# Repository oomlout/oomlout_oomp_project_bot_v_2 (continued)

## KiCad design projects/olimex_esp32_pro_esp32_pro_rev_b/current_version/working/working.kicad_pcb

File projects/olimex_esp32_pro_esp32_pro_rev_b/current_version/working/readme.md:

# esp32_pro
 
## summary 
* id: olimex_esp32_pro_esp32_pro_rev_b
* user: olimex
* name: esp32_pro
* board: esp32_pro_rev_b
* repo: https://github.com/OLIMEX/ESP32-PRO
* src_file_repo_kicad_pcb: HARDWARE/REV-B/ESP32-PRO_Rev_B.kicad_pcb
* src_file_repo_kicad_pcb_link: https://github.com/OLIMEX/ESP32-PRO/tree/master/HARDWARE/REV-B/ESP32-PRO_Rev_B.kicad_pcb

* src_file_repo_sch: HARDWARE/REV-B/ESP32-PRO_Rev_B.sch
* src_file_repo_sch_link: https://github.com/OLIMEX/ESP32-PRO/tree/master/HARDWARE/REV-B/ESP32-PRO_Rev_B.sch
* full details link: https://github.com/oomlout/oomlout_oomp_project_bot_v_2/tree/main/projects/olimex_esp32_pro_esp32_pro_rev_b/current_version/working

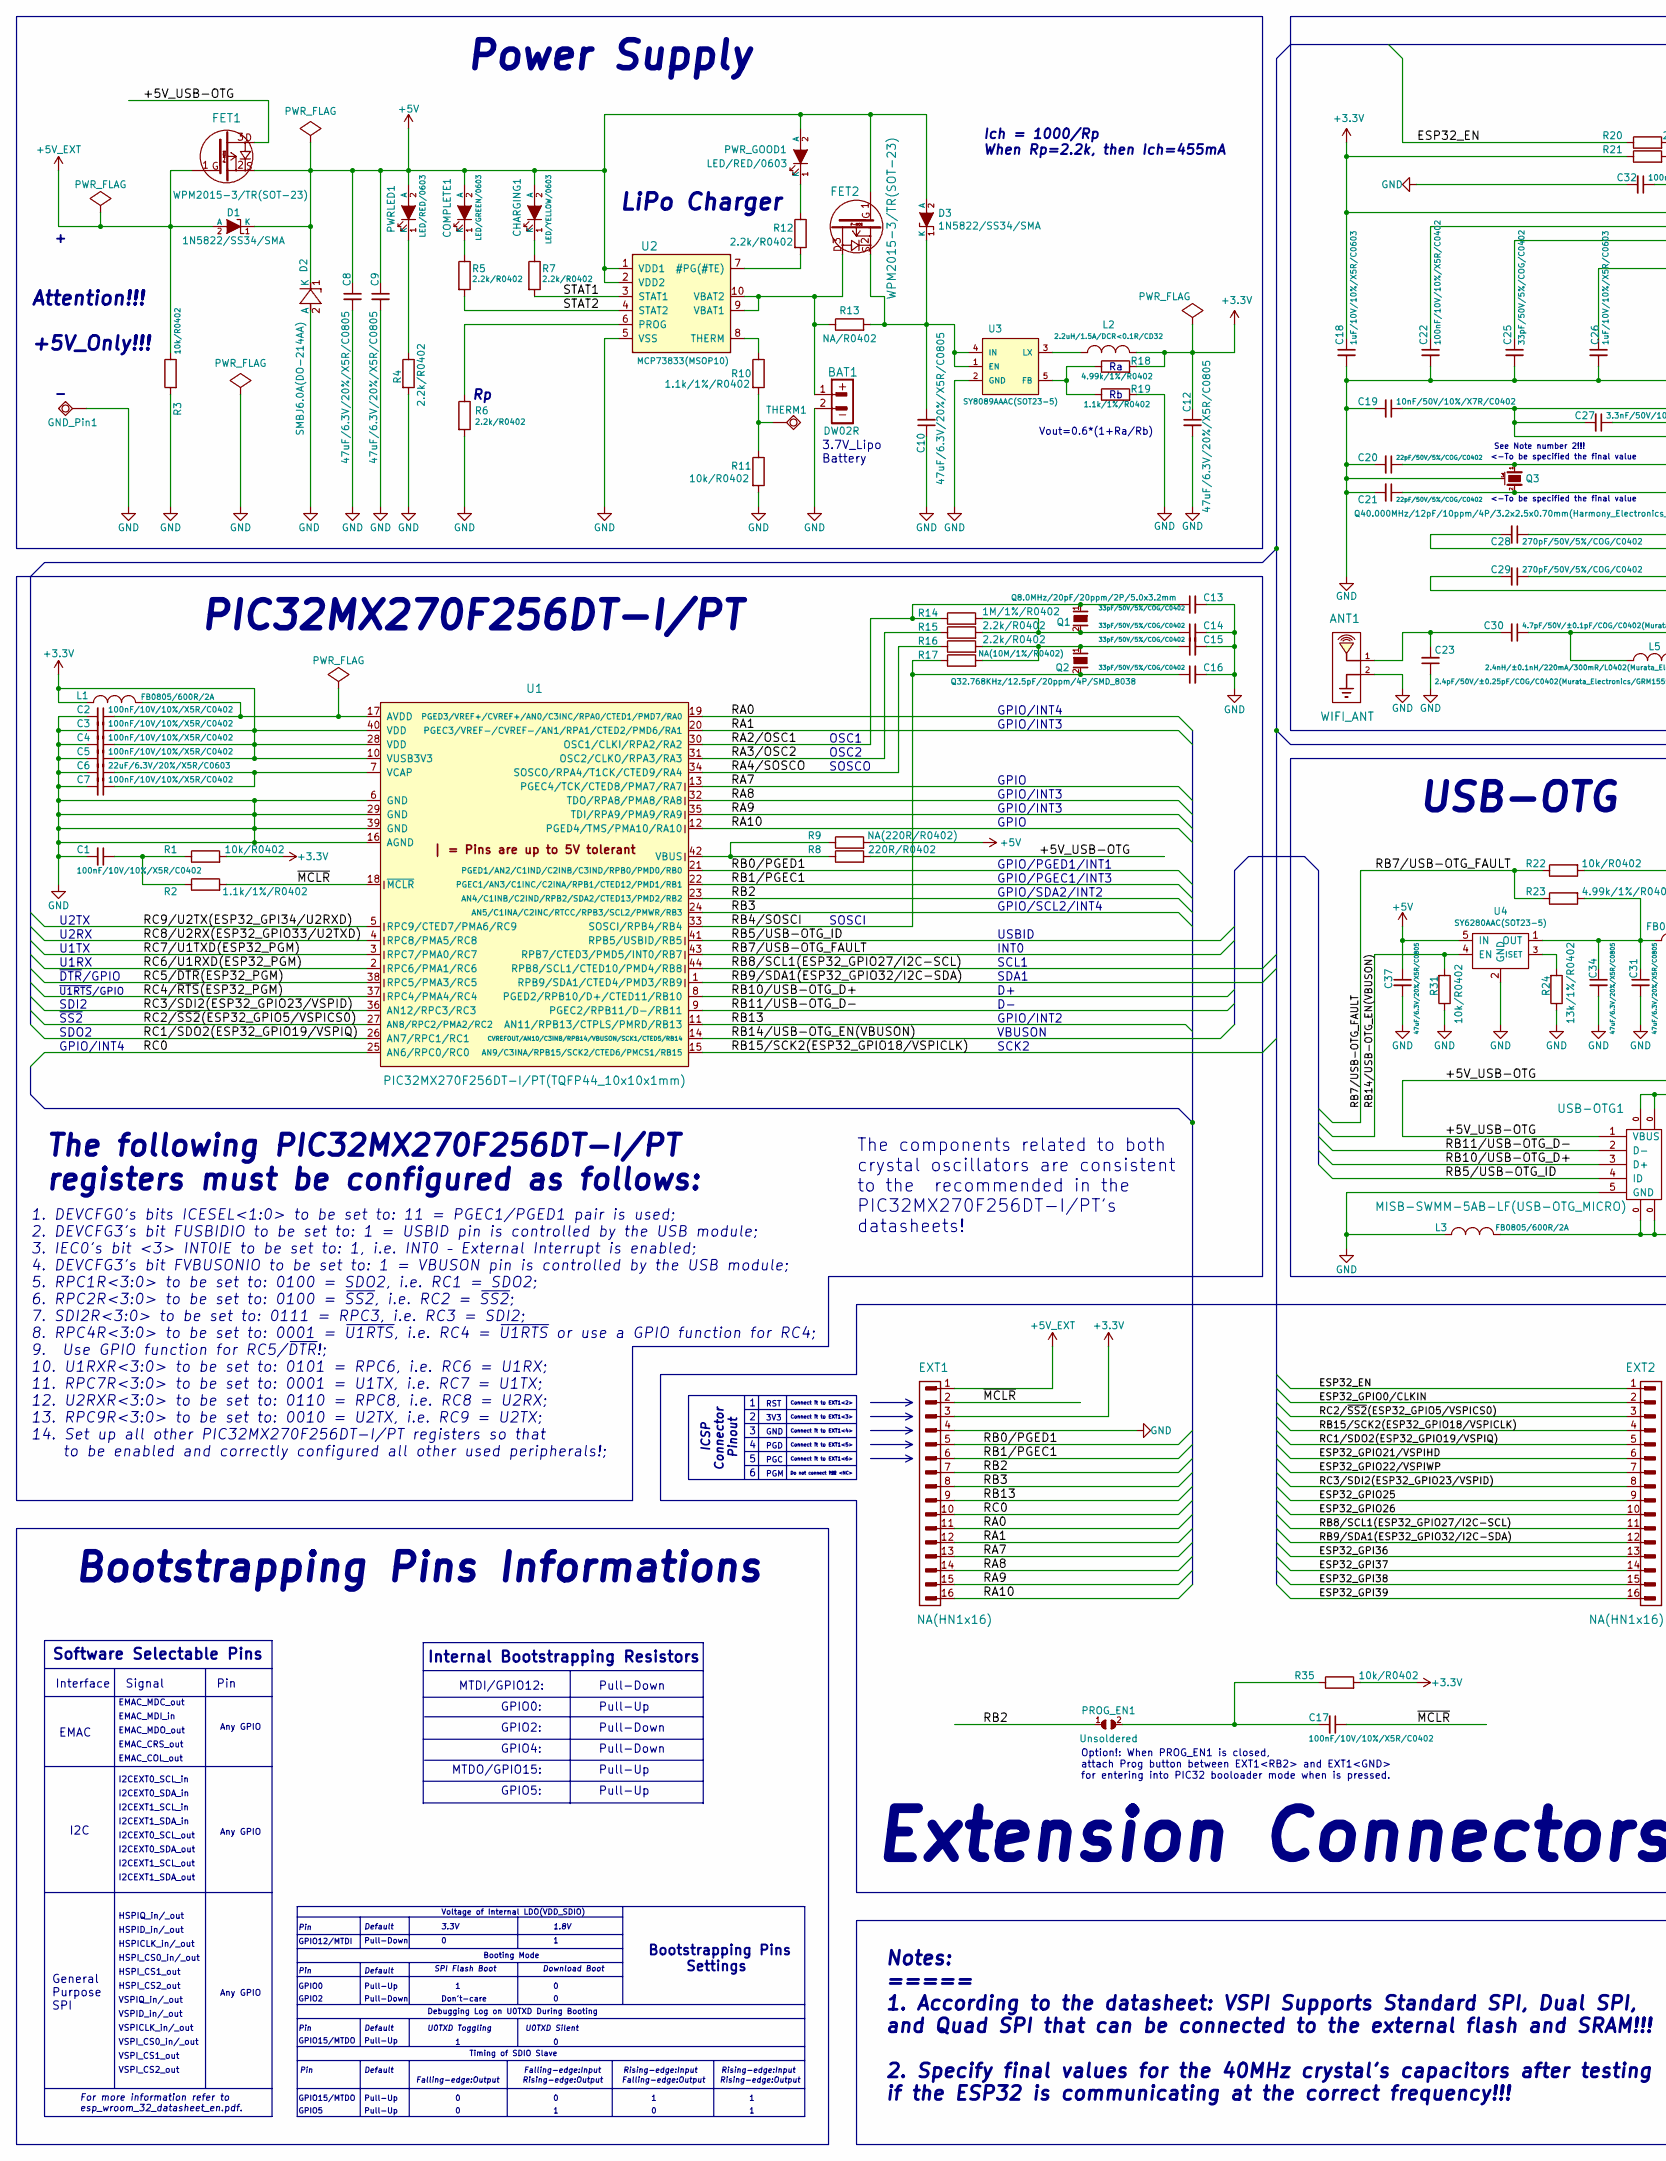
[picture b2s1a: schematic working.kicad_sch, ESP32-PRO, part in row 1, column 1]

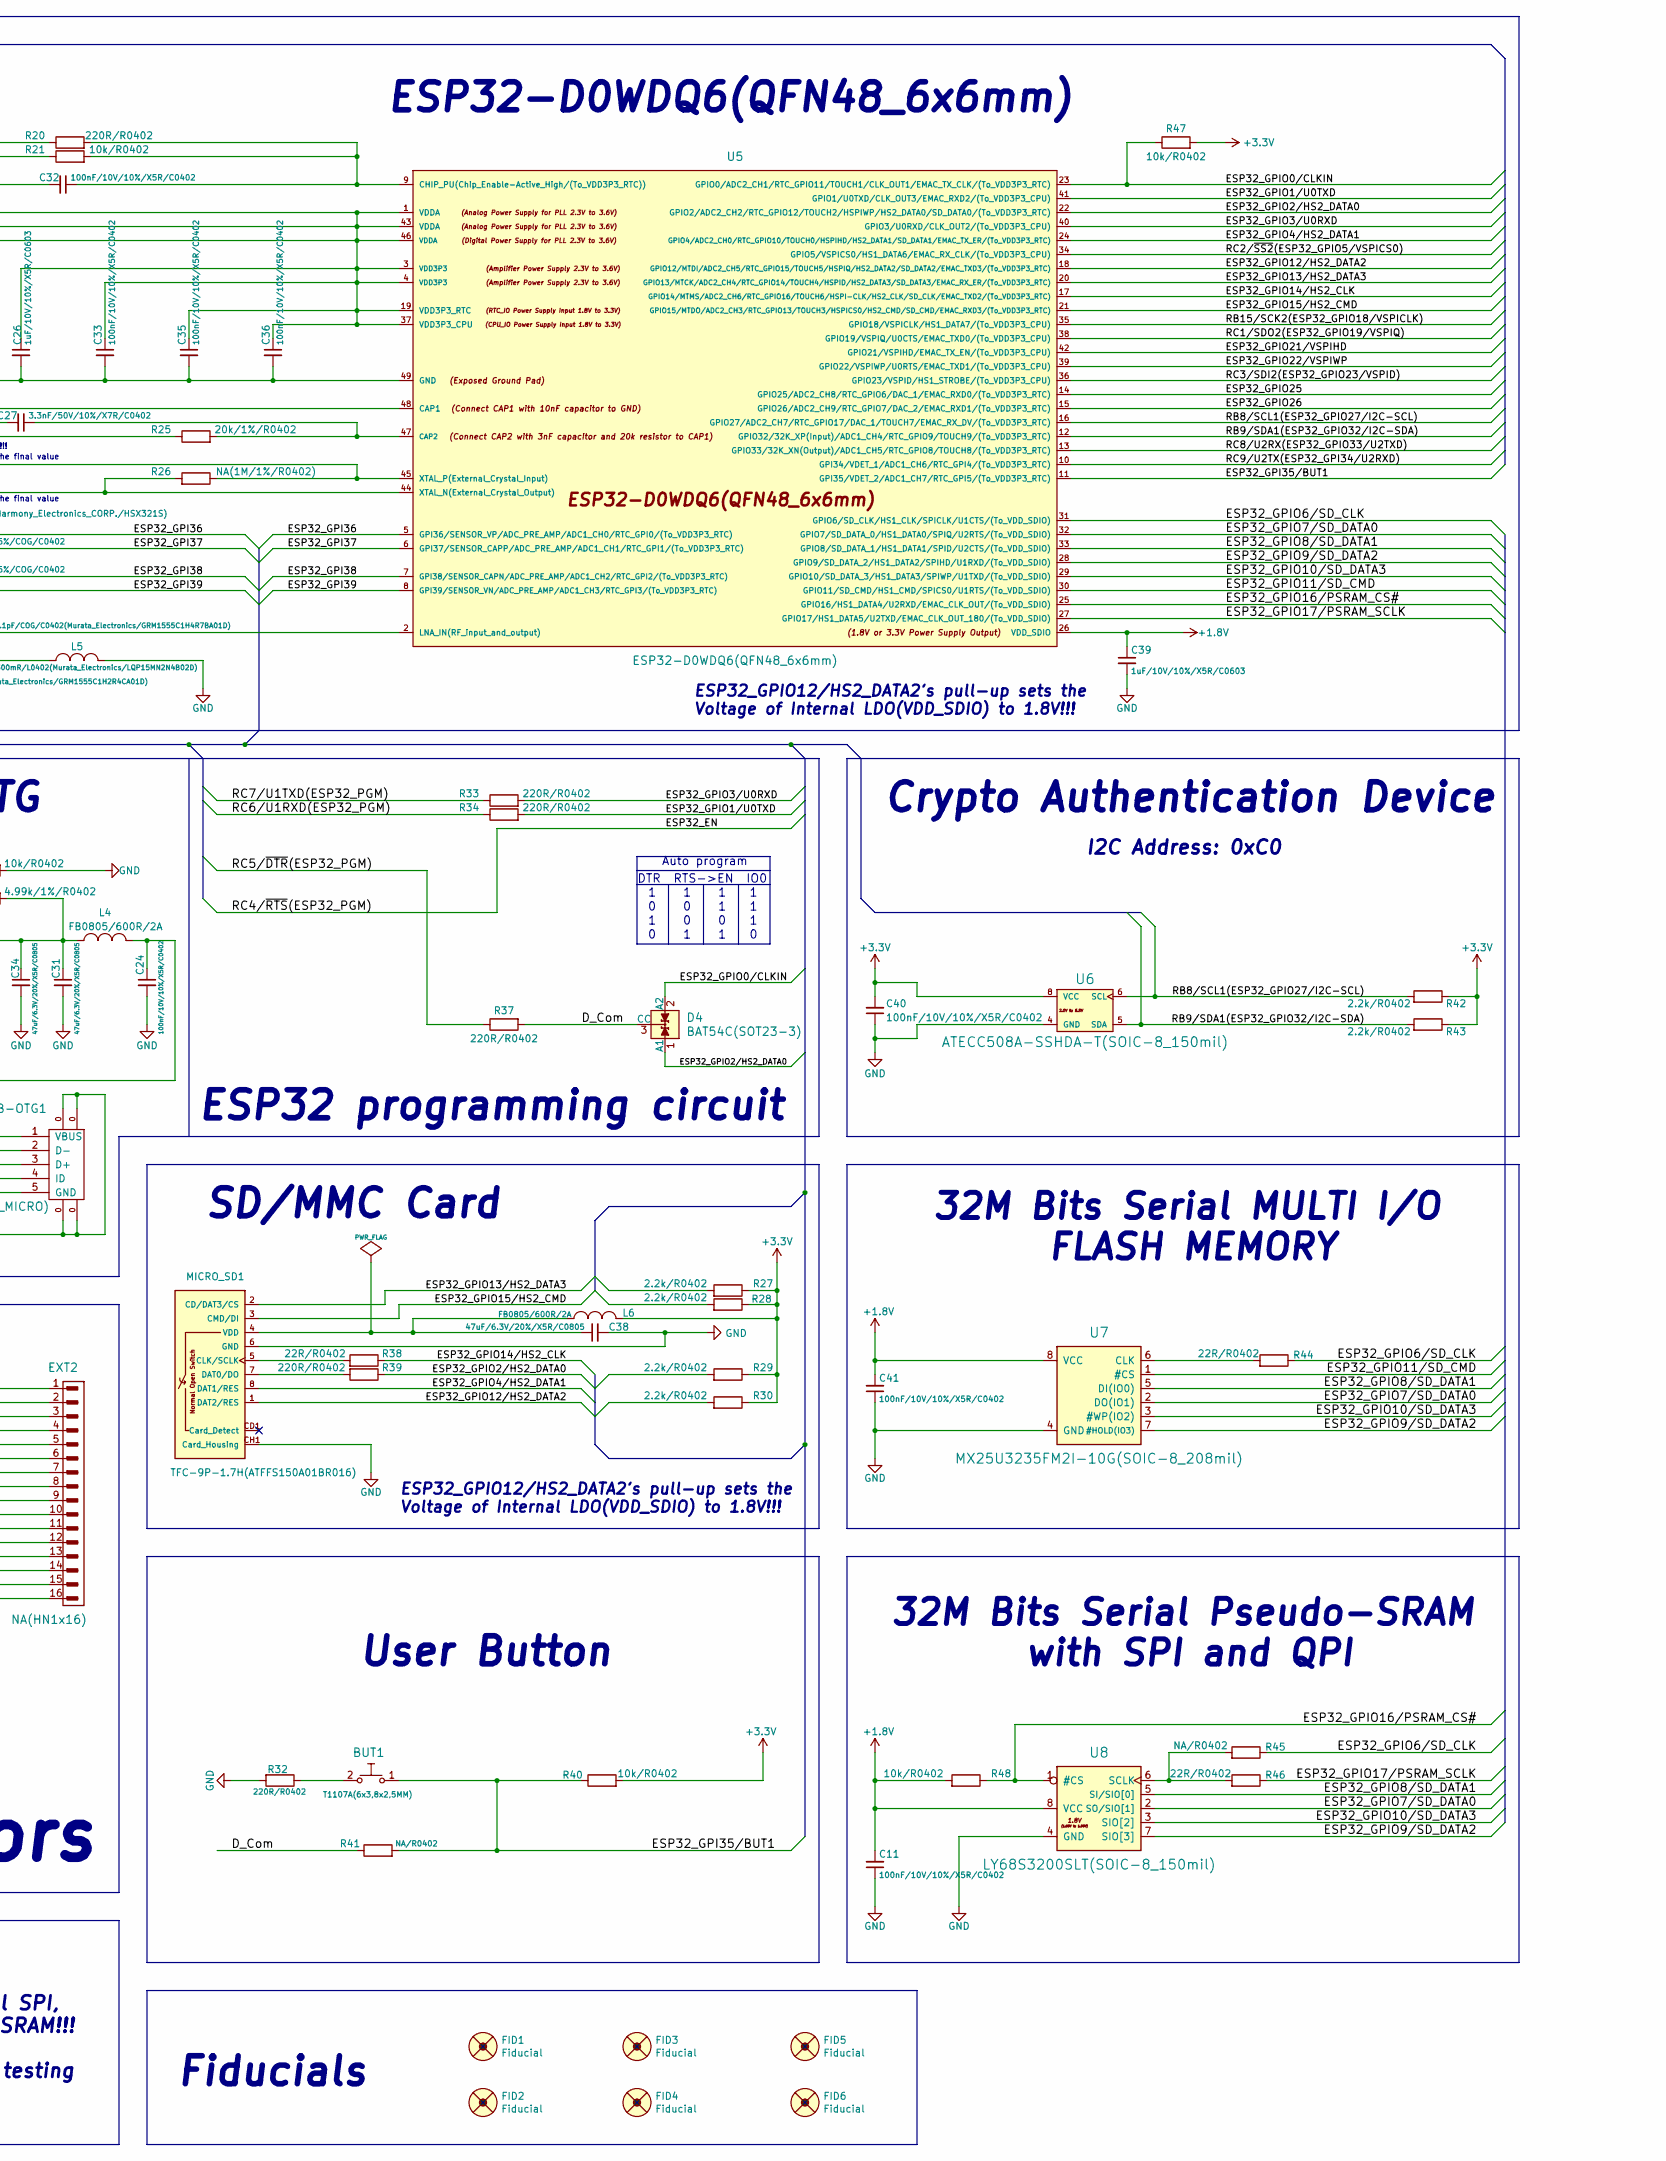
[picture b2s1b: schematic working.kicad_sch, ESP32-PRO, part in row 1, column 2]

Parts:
ANT1: WIFI_ANT; BT_Antenna_Inverted_1ANT_2GND
BAT1: DW02R; LIPO_BAT-CON2DW02R
BUT1: T1107A(6x3,8x2,5MM)
C1, C2, C3, C4, C5, C7, C11, C17, C22, C24, C32, C33, C35, C36, C40, C41: 100nF/10V/10%/X5R/C0402; C_0402_5MIL_DWS
C6: 22uF/6.3V/20%/X5R/C0603; C_0603_5MIL_DWS
C8, C9, C10, C12, C31, C34, C37, C38: 47uF/6.3V/20%/X5R/C0805; C_0805_5MIL_DWS
C13, C14, C15, C16, C25: 33pF/50V/5%/COG/C0402; C_0402_5MIL_DWS
C18, C26, C39: 1uF/10V/10%/X5R/C0603; C_0603_5MIL_DWS
C19: 10nF/50V/10%/X7R/C0402; C_0402_5MIL_DWS
C20, C21: 22pF/50V/5%/COG/C0402; C_0402_5MIL_DWS
C23: 2.4pF/50V/±0.25pF/COG/C0402(Murata_Electronics/GR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; C_0402_5MIL_DWS
C27: 3.3nF/50V/10%/X7R/C0402; C_0402_5MIL_DWS
C28, C29: 270pF/50V/5%/COG/C0402; C_0402_5MIL_DWS
C30: 4.7pF/50V/±0.1pF/COG/C0402(Murata_Electronics/GRM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; C_0402_5MIL_DWS
CHARGING1: LED/YELLOW/0603; LED_0603_KA
COMPLETE1: LED/GREEN/0603; LED_0603_KA
D1, D3: 1N5822/SS34/SMA; SMA-KA
D2: SMBJ6.0A(DO-214AA); DO214AA_1(K)-2(A)
D4: BAT54C(SOT23-3); SOT23-3
EXT1, EXT2: NA(HN1x16); HN1x16
FET1, FET2: WPM2015-3/TR(SOT-23); SOT23
FID1, FID2, FID3, FID4, FID5, FID6: Fiducial; Fiducial1x3
GND_Pin1: TESTPAD; TESTPAD_40-ROUND
L1, L3, L4, L6: FB0805/600R/2A; L_0805_5MIL_DWS
L2: 2.2uH/1.5A/DCR<0.1R/CD32; CD32
L5: 2.4nH/±0.1nH/220mA/300mR/L0402(Murata_Electronics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; L_0402_5MIL_DWS
MICRO_SD1: TFC-9P-1.7H(ATFFS150A01BR016); uSD(TFC-9P-1.xH(ATFFS150A01BR016))
PROG_EN1: Unsoldered; SJ
PWRLED1: LED/RED/0603; LED_0603_KA
PWR_GOOD1: LED/RED/0603; LED_0603_KA
Q1: Q8.0MHz/20pF/20ppm/2P/5.0x3.2mm; HCX-4S_2Pins_5.0x3.2mm
Q2: Q32.768KHz/12.5pF/20ppm/4P/SMD_8038; MC306-HS
Q3: Q40.000MHz/12pF/10ppm/4P/3.2x2.5x0.70mm(Harmony_E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; TSX-3.2x2.5mm_GND(3)
R1, R3, R11, R21, R22, R31, R35, R40, R47, R48: 10k/R0402; R_0402_5MIL_DWS
R2, R10, R19: 1.1k/1%/R0402; R_0402_5MIL_DWS
R4, R5, R6, R7, R12, R15, R16, R27, R28, R29, R30, R42, R43: 2.2k/R0402; R_0402_5MIL_DWS
R8, R20, R32, R33, R34, R37, R39: 220R/R0402; R_0402_5MIL_DWS
R9: NA(220R/R0402); R_0402_5MIL_DWS
R13, R41, R45: NA/R0402; R_0402_5MIL_DWS
R14: 1M/1%/R0402; R_0402_5MIL_DWS
R17: NA(10M/1%/R0402); R_0402_5MIL_DWS
R18, R23: 4.99k/1%/R0402; R_0402_5MIL_DWS
R24: 13k/1%/R0402; R_0402_5MIL_DWS
R25: 20k/1%/R0402; R_0402_5MIL_DWS
R26: NA(1M/1%/R0402); R_0402_5MIL_DWS
R38, R44, R46: 22R/R0402; R_0402_5MIL_DWS
THERM1: TESTPAD; TESTPAD_40-ROUND
U1: PIC32MX270F256DT-I/PT(TQFP44_10x10x1mm); TQFP44
U2: MCP73833(MSOP10); MSOP-10_Pitch-0.5mm_3.00x3.00x1.00mm
U3: SY8089AAAC(SOT23-5); SOT-23-5
U4: SY6280AAC(SOT23-5); SOT-23-5
U5: ESP32-D0WDQ6(QFN48_6x6mm); QFN48-6x6mm-OLIMEX_V2
U6: ATECC508A-SSHDA-T(SOIC-8_150mil); SOIC-8_150mil
U7: MX25U3235FM2I-10G(SOIC-8_208mil); SO-8_208mil
U8: LY68S3200SLT(SOIC-8_150mil); SOIC-8_150mil
USB-OTG1: MISB-SWMM-5AB-LF(USB-OTG_MICRO); USB-MICRO_MISB-SWMM-5B_LF

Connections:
+1V8: C11.2, C39.1, C41.2, R48.2, U5.26 (VDD_SDIO), U7.8 (VCC), U8.8 (VCC)
+3V3: C3.1, C4.1, C5.1, C12.1, C18.1, C22.1, C25.1, C26.1, C33.1, C35.1, C36.1, C40.2, EXT1.3, L1.1, L2.2, L6.1, R1.2, R18.2, R21.1, R27.1, R28.1, R29.1, R30.1, R35.2, R40.2, R42.1, R43.1, R47.2, U1.10 (VUSB3V3), U1.28 (VDD), U1.40 (VDD), U5.1 (VDDA), U5.3 (VDD3P3), U5.4 (VDD3P3), U5.19 (VDD3P3_RTC), U5.37 (VDD3P3_CPU), U5.43 (VDDA), U5.46 (VDDA), U6.8 (VCC)
+5V: C8.1, C9.1, C37.1, CHARGING1.2 (A), COMPLETE1.2 (A), D1.1 (K), D2.1 (K), D3.2 (A), FET1.2, FET2.1, PWRLED1.2 (A), PWR_GOOD1.2 (A), R9.2, U2.1 (VDD1), U2.2 (VDD2), U4.5 (IN)
+5V_EXT: D1.2 (A), EXT1.1, FET1.1, R3.1
/+5V_USB-OTG: C24.1, FET1.3, L4.1, R8.2, USB-OTG1.1 (VBUS)
/D_Com: D4.3 (CC), R37.2, R41.1
/ESP32_EN: EXT2.1, R20.1, U1.37 (RPC4/PMA4/RC4)
/ESP32_GPI35/BUT1: BUT1.1, R40.1, R41.2, U5.11 (GPI35/VDET_2/ADC1_CH7/RTC_GPI5/(To_VDD3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)
/ESP32_GPI36: C28.1, EXT2.13, U5.5 (GPI36/SENSOR_VP/ADC_PRE_AMP/ADC1_CH0/RT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)
/ESP32_GPI37: C28.2, EXT2.14, U5.6 (GPI37/SENSOR_CAPP/ADC_PRE_AMP/ADC1_CH1/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)
/ESP32_GPI38: C29.1, EXT2.15, U5.7 (GPI38/SENSOR_CAPN/ADC_PRE_AMP/ADC1_CH2/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)
/ESP32_GPI39: C29.2, EXT2.16, U5.8 (GPI39/SENSOR_VN/ADC_PRE_AMP/ADC1_CH3/RT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)
/ESP32_GPIO0/CLKIN: D4.2 (A2), EXT2.2, R47.1, U5.23 (GPIO0/ADC2_CH1/RTC_GPIO11/TOUCH1/CLK_OU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)
/ESP32_GPIO1/U0TXD: R34.2, U5.41 (GPIO1/U0TXD/CLK_OUT3/EMAC_RXD2/(To_VDD3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)
/ESP32_GPIO2/HS2_DATA0: D4.1 (A1), R29.2, R39.1, U5.22 (GPIO2/ADC2_CH2/RTC_GPIO12/TOUCH2/HSPIWP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)
/ESP32_GPIO3/U0RXD: R33.2, U5.40 (GPIO3/U0RXD/CLK_OUT2/(To_VDD3P3_CPU))
/ESP32_GPIO4/HS2_DATA1: MICRO_SD1.8 (DAT1/RES), U5.24 (GPIO4/ADC2_CH0/RTC_GPIO10/TOUCH0/HSPIHD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)
/ESP32_GPIO6/SD_CLK: R44.1, R45.1, U5.31 (GPIO6/SD_CLK/HS1_CLK/SPICLK/U1CTS/(To_V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)
/ESP32_GPIO7/SD_DATA0: U5.32 (GPIO7/SD_DATA_0/HS1_DATA0/SPIQ/U2RTS/(T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), U7.2 (DO(IO1)), U8.2 (SO/SIO[1])
/ESP32_GPIO8/SD_DATA1: U5.33 (GPIO8/SD_DATA_1/HS1_DATA1/SPID/U2CTS/(T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), U7.5 (DI(IO0)), U8.5 (SI/SIO[0])
/ESP32_GPIO9/SD_DATA2: U5.28 (GPIO9/SD_DATA_2/HS1_DATA2/SPIHD/U1RXD/(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), U7.7 (#HOLD(IO3)), U8.7 (SIO[3])
/ESP32_GPIO10/SD_DATA3: U5.29 (GPIO10/SD_DATA_3/HS1_DATA3/SPIWP/U1TXD/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), U7.3 (#WP(IO2)), U8.3 (SIO[2])
/ESP32_GPIO11/SD_CMD: U5.30 (GPIO11/SD_CMD/HS1_CMD/SPICS0/U1RTS/(To_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), U7.1 (#CS)
/ESP32_GPIO12/HS2_DATA2: MICRO_SD1.1 (DAT2/RES), R30.2, U5.18 (GPIO12/MTDI/ADC2_CH5/RTC_GPIO15/TOUCH5/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)
/ESP32_GPIO13/HS2_DATA3: MICRO_SD1.2 (CD/DAT3/CS), R27.2, U5.20 (GPIO13/MTCK/ADC2_CH4/RTC_GPIO14/TOUCH4/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)
/ESP32_GPIO14/HS2_CLK: R38.1, U5.17 (GPIO14/MTMS/ADC2_CH6/RTC_GPIO16/TOUCH6/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)
/ESP32_GPIO15/HS2_CMD: MICRO_SD1.3 (CMD/DI), R28.2, U5.21 (GPIO15/MTDO/ADC2_CH3/RTC_GPIO13/TOUCH3/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)
/ESP32_GPIO16/PSRAM_CS#: R48.1, U5.25 (GPIO16/HS1_DATA4/U2RXD/EMAC_CLK_OUT/(To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), U8.1 (#CS)
/ESP32_GPIO17/PSRAM_SCLK: R46.1, U5.27 (GPIO17/HS1_DATA5/U2TXD/EMAC_CLK_OUT_180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)
/ESP32_GPIO21/VSPIHD: EXT2.6, U5.42 (GPIO21/VSPIHD/EMAC_TX_EN/(To_VDD3P3_CPU))
/ESP32_GPIO22/VSPIWP: EXT2.7, U5.39 (GPIO22/VSPIWP/U0RTS/EMAC_TXD1/(To_VDD3P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)
/ESP32_GPIO25: EXT2.9, U5.14 (GPIO25/ADC2_CH8/RTC_GPIO6/DAC_1/EMAC_RX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)
/ESP32_GPIO26: EXT2.10, U5.15 (GPIO26/ADC2_CH9/RTC_GPIO7/DAC_2/EMAC_RX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)
/RA0: EXT1.11, U1.19 (PGED3/VREF+/CVREF+/AN0/C3INC/RPA0/CTED1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)
/RA1: EXT1.12, U1.20 (PGEC3/VREF-/CVREF-/AN1/RPA1/CTED2/PMD6/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)
/RA2/OSC1: C13.1, Q1.1, R14.1, U1.30 (OSC1/CLKI/RPA2/RA2)
/RA3/OSC2: R15.1, U1.31 (OSC2/CLKO/RPA3/RA3)
/RA4/SOSCO: R16.1, U1.34 (SOSCO/RPA4/T1CK/CTED9/RA4)
/RA7: EXT1.13, U1.13 (PGEC4/TCK/CTED8/PMA7/RA7)
/RA8: EXT1.14, U1.32 (TDO/RPA8/PMA8/RA8)
/RA9: EXT1.15, U1.35 (TDI/RPA9/PMA9/RA9)
/RA10: EXT1.16, U1.12 (PGED4/TMS/PMA10/RA10)
/RB0/PGED1: EXT1.5, U1.21 (PGED1/AN2/C1IND/C2INB/C3IND/RPB0/PMD0/R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)
/RB1/PGEC1: EXT1.6, U1.22 (PGEC1/AN3/C1INC/C2INA/RPB1/CTED12/PMD1/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)
/RB2: EXT1.7, PROG_EN1.1, U1.23 (AN4/C1INB/C2IND/RPB2/SDA2/CTED13/PMD2/R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)
/RB3: EXT1.8, U1.24 (AN5/C1INA/C2INC/RTCC/RPB3/SCL2/PMWR/RB3)
/RB4/SOSCI: C16.1, Q2.2, R17.1, U1.33 (SOSCI/RPB4/RB4)
/RB5/USB-OTG_ID: U1.41 (RPB5/USBID/RB5), USB-OTG1.4 (ID)
/RB7/USB-OTG_FAULT: R22.1, R23.1, U1.43 (RPB7/CTED3/PMD5/INT0/RB7)
/RB8/SCL1(ESP32_GPIO27/I2C-SCL): EXT2.11, R42.2, U1.44 (RPB8/SCL1/CTED10/PMD4/RB8), U5.16 (GPIO27/ADC2_CH7/RTC_GPIO17/DAC_1/TOUCH7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), U6.6 (SCL)
/RB9/SDA1(ESP32_GPIO32/I2C-SDA): EXT2.12, R43.2, U1.1 (RPB9/SDA1/CTED4/PMD3/RB9), U5.12 (GPIO32/32K_XP(Input)/ADC1_CH4/RTC_GPIO9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), U6.5 (SDA)
/RB10/USB-OTG_D+: U1.8 (PGED2/RPB10/D+/CTED11/RB10), USB-OTG1.3 (D+)
/RB11/USB-OTG_D-: U1.9 (PGEC2/RPB11/D-/RB11), USB-OTG1.2 (D-)
/RB13: EXT1.9, U1.11 (AN11/RPB13/CTPLS/PMRD/RB13)
/RB14/USB-OTG_EN(VBUSON): R31.2, U1.14 (CVREFOUT/AN10/C3INB/RPB14/VBUSON/SCK1/C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), U4.4 (EN)
/RB15/SCK2(ESP32_GPIO18/VSPICLK): EXT2.4, U1.15 (AN9/C3INA/RPB15/SCK2/CTED6/PMCS1/RB15), U5.35 (GPIO18/VSPICLK/HS1_DATA7/(To_VDD3P3_CPU))
/RC0: EXT1.10, U1.25 (AN6/RPC0/RC0)
/RC1/SDO2(ESP32_GPIO19/VSPIQ): EXT2.5, U1.26 (AN7/RPC1/RC1), U5.38 (GPIO19/VSPIQ/U0CTS/EMAC_TXD0/(To_VDD3P3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)
/RC2/~SS2(ESP32_GPIO5/VSPICS0): EXT2.3, U1.27 (AN8/RPC2/PMA2/RC2), U5.34 (GPIO5/VSPICS0/HS1_DATA6/EMAC_RX_CLK/(To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)
/RC3/SDI2(ESP32_GPIO23/VSPID): EXT2.8, U1.36 (AN12/RPC3/RC3), U5.36 (GPIO23/VSPID/HS1_STROBE/(To_VDD3P3_CPU))
/RC5/~DTR(ESP32_PGM): R37.1, U1.38 (RPC5/PMA3/RC5)
/RC6/U1RXD(ESP32_PGM): R34.1, U1.2 (RPC6/PMA1/RC6)
/RC7/U1TXD(ESP32_PGM): R33.1, U1.3 (RPC7/PMA0/RC7)
/RC8/U2RX(ESP32_GPIO33/U2TXD): U1.4 (RPC8/PMA5/RC8), U5.13 (GPIO33/32K_XN(Output)/ADC1_CH5/RTC_GPIO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)
/RC9/U2TX(ESP32_GPI34/U2RXD): U1.5 (RPC9/CTED7/PMA6/RC9), U5.10 (GPI34/VDET_1/ADC1_CH6/RTC_GPI4/(To_VDD3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)
/STAT1: R7.2, U2.3 (STAT1)
/STAT2: R5.2, U2.4 (STAT2)
/~MCLR: C17.1, EXT1.2, R2.2, U1.18 (~MCLR)
GND: ANT1.2, BAT1.2, C1.2, C2.2, C3.2, C4.2, C5.2, C6.2, C7.2, C8.2, C9.2, C10.1, C11.1, C12.2, C13.2, C14.2, C15.2, C16.2, C18.2, C19.2, C20.2, C21.2, C22.2, C23.1, C24.2, C25.2, C26.2, C31.2, C32.2, C33.2, C34.2, C35.2, C36.2, C37.2, C38.2, C39.2, C40.1, C41.1, D2.2 (A), EXT1.4, GND_Pin1.1, L3.2, L5.2, MICRO_SD1.6 (GND), MICRO_SD1.CH1 (Card_Housing), Q3.3 (case), R3.2, R4.2, R6.2, R11.2, R19.2, R22.2, R24.1, R31.1, R32.2, U1.6 (GND), U1.16 (AGND), U1.29 (GND), U1.39 (GND), U2.5 (VSS), U3.2 (GND), U4.2 (GND), U5.49 (GND), U6.4 (GND), U7.4 (GND), U8.4 (GND), USB-OTG1.5 (GND)
unnamed: ANT1.1, C23.2, C30.2
unnamed: BAT1.1, FET2.3, R13.1, U2.9 (VBAT1), U2.10 (VBAT2)
unnamed: BUT1.2, R32.1
unnamed: C1.1, R1.1, R2.1
unnamed: C2.1, L1.2, U1.17 (AVDD)
unnamed: C6.1, C7.1, U1.7 (VCAP)
unnamed: C10.2, D3.1 (K), FET2.2, R13.2, U3.1 (EN), U3.4 (IN)
unnamed: C14.1, Q1.2, R14.2, R15.2
unnamed: C15.1, Q2.1, R16.2, R17.2
unnamed: C17.2, PROG_EN1.2, R35.1
unnamed: C19.1, C27.2, R25.1, U5.48 (CAP1)
unnamed: C20.1, Q3.1, R26.1, U5.45 (XTAL_P(External_Crystal_Input))
unnamed: C21.1, Q3.2, R26.2, U5.44 (XTAL_N(External_Crystal_Output))
unnamed: C27.1, R25.2, U5.47 (CAP2)
unnamed: C30.1, L5.1, U5.2 (LNA_IN(RF_input_and_output))
unnamed: C31.1, C34.1, L4.2, R23.2, U4.1 (OUT)
unnamed: C32.1, R20.2, R21.2, U5.9 (CHIP_PU(Chip_Enable-Active_High/(To_VDD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)
unnamed: C38.1, L6.2, MICRO_SD1.4 (VDD)
unnamed: CHARGING1.1 (K), R7.1
unnamed: COMPLETE1.1 (K), R5.1
unnamed: L2.1, U3.3 (LX)
unnamed: L3.1, USB-OTG1.0
unnamed: MICRO_SD1.5 (CLK/SCLK), R38.2
unnamed: MICRO_SD1.7 (DAT0/DO), R39.2
unnamed: PWRLED1.1 (K), R4.1
unnamed: PWR_GOOD1.1 (K), R12.1
unnamed: R6.1, U2.6 (PROG)
unnamed: R8.1, R9.1, U1.42 (VBUS)
unnamed: R10.1, U2.8 (THERM)
unnamed: R10.2, R11.1, THERM1.1
unnamed: R12.2, U2.7 (#PG(#TE))
unnamed: R18.1, R19.1, U3.5 (FB)
unnamed: R24.2, U4.3 (ISET)
unnamed: R44.2, U7.6 (CLK)
unnamed: R45.2, R46.2, U8.6 (SCLK)

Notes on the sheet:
The components related to both crystal oscillators are consistent to the recommended in the PIC32MX270F256DT-I/PT's datasheets!
Any GPIO
Default
ESP32 programming circuit
Vout=0.6*(1+Ra/Rb)
32M Bits Serial MULTI I/O FLASH MEMORY
GPIO5:
OSC2
<-To be specified the final value
Rising-edge:Output
<-To be specified the final value
Pull-Down
U0TXD Toggling
Attention!!! +5V_Only!!!
HSPICLK_in/_out
SPI Flash Boot
DTR RTS->EN IO0
VSPI_CS2_out
SCK2
I2CEXT1_SDA_in
I2CEXT1_SCL_out
Pin
Internal Bootstrapping Resistors
Timing of SDIO Slave
I2CEXT0_SCL_in
Pull-Up
GPIO/INT3
Connect it to EXT1<5>
~{SS2}
GPIO/INT4
Connect it to EXT1<6>
SDA1
ESP32_GPIO12/HS2_DATA2's pull-up sets the Voltage of Internal LDO(VDD_SDIO) to 1.8V!!!
SD/MMC Card
GPIO/SCL2/INT4
PIC32MX270F256DT-I/PT
HSPI_CS1_out
Fiducials
U2TX
ESP32-D0WDQ6(QFN48_6x6mm)

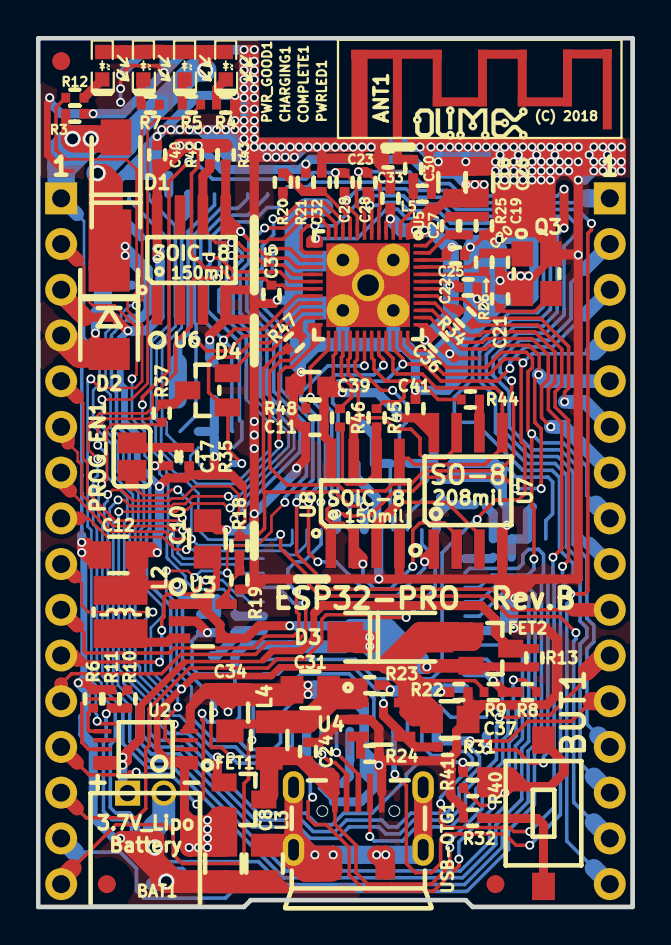
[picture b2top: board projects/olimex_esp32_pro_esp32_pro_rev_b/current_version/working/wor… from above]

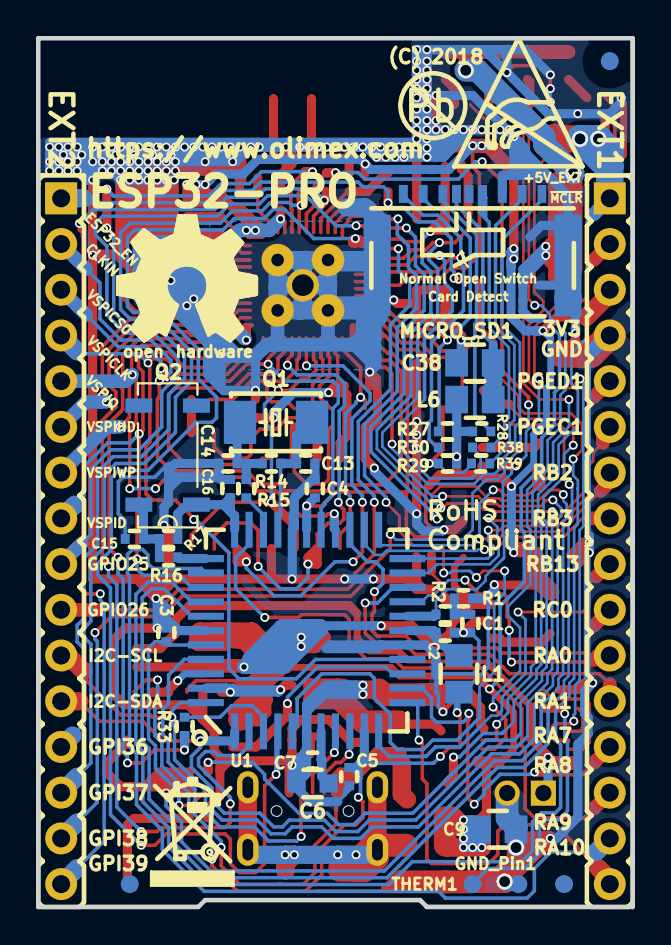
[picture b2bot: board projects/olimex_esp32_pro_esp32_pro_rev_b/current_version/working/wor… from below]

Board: 2 copper layers, 33.0 x 48.3 mm, 132 parts (40 on the bottom side), 104 nets.

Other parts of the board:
Ref**: Val**; LOGO_ANTISTATIC_1
